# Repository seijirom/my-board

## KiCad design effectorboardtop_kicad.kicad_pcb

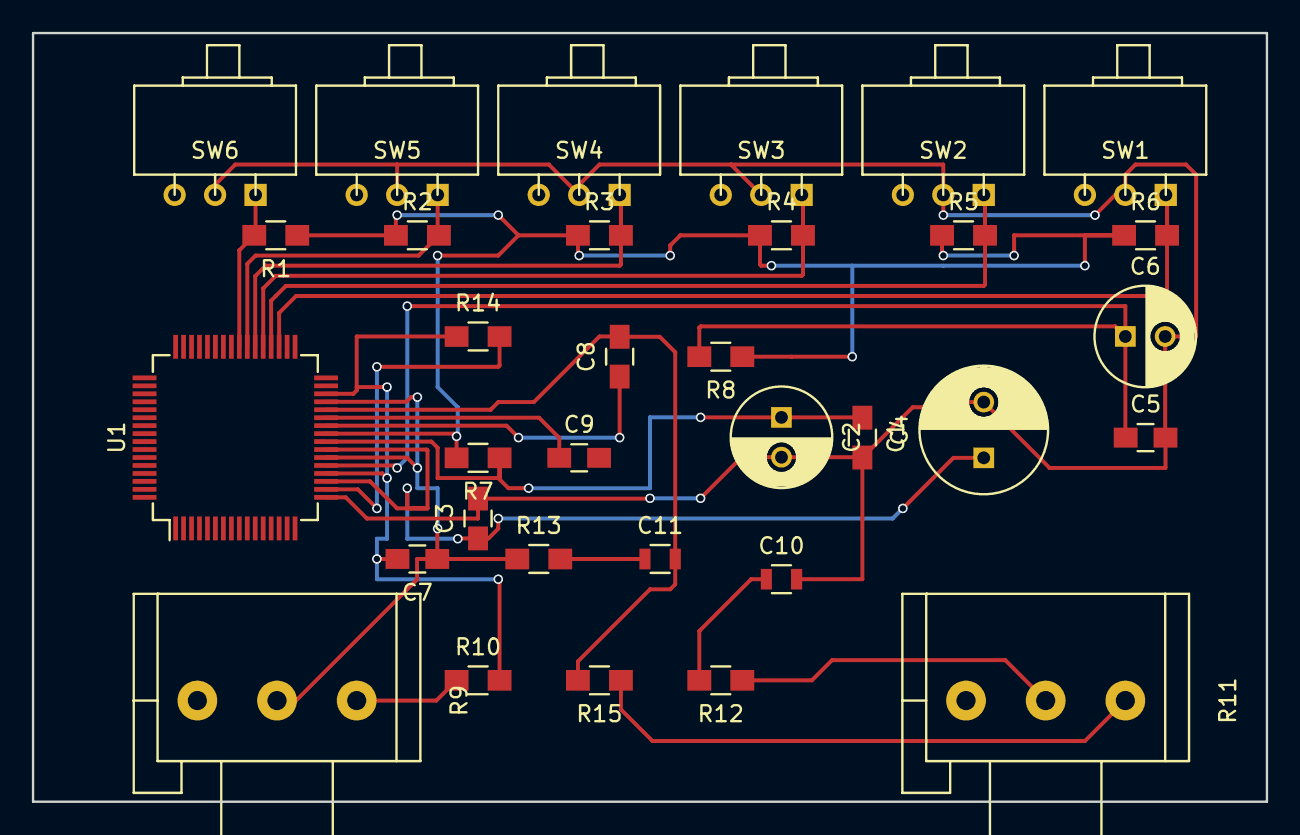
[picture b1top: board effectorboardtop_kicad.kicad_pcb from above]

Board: 2 copper layers, 77.5 x 48.3 mm, 33 parts (0 on the bottom side), 22 nets.

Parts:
C1, C3, C5: 0.1u; C_0805_HandSoldering
C2, C6: 100u; C_Radial_D6.3_L11.2_P2.5
C4: 470u; C_Radial_D8_L11.5_P3.5
C7: 47p; C_0805_HandSoldering
C8: 100p; C_0805_HandSoldering
C9: 0.047u; C_0805_HandSoldering
C10: 0.1u; R_0805
C11: 0.47u; R_0805
R1, R2, R3, R4, R5, R6, R12: 47k; R_0805_HandSoldering
R7, R8: 67k; R_0805_HandSoldering
R9: 500k; Potentiometer_Alps-RK16-single
R10, R13, R15: 10k; R_0805_HandSoldering
R11: 47k; Potentiometer_Alps-RK16-single
R14: 20k; R_0805_HandSoldering
SW1, SW2, SW3, SW4, SW5, SW6: SPST; SW_Micro_SPST_Angled
U1: QFP05-64; TQFP-64_10x10mm_Pitch0.5mm

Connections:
GND: C1.2, C2.2, C3.2, C4.2, C5.2, C6.2, C10.2, SW1.2, SW2.2, SW3.2, SW4.2, SW5.2, SW6.2, U1.17
unnamed: R1.1, R2.1, R3.1, R4.1, R5.1, R6.1, R7.2, R8.1, U1.25
unnamed: C1.1, C2.1, R7.1, U1.24
unnamed: C3.1, C4.1, U1.19, U1.23
unnamed: C5.1, C6.1, R8.2, U1.21
unnamed: C7.1, R9.2, R13.1, U1.22, U1.29
unnamed: C7.2, R10.2, R14.1, U1.20, U1.30
unnamed: C8.1, U1.26
unnamed: C9.1, U1.27
unnamed: C10.1, R12.2
unnamed: C11.1, R13.2
unnamed: C8.2, C11.2, R15.2, U1.28
unnamed: R14.2, U1.18
unnamed: R1.2, SW6.1, U1.40
unnamed: R2.2, SW5.1, U1.39
unnamed: R3.2, SW4.1, U1.38
unnamed: R4.2, SW3.1, U1.37
unnamed: R5.2, SW2.1, U1.36
unnamed: R6.2, SW1.1, U1.35
unnamed: R9.1, R10.1
unnamed: R11.1, R15.1
unnamed: R11.2, R12.1

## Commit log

2016-05-13 Add C:\Users\seijirom\AppData\Roaming\ALB\kicad\my_board_HEAD
2016-05-14 pcb layout first trial
2016-05-14 kicad_pcb added
2016-05-15 placement and routing completed
2016-05-15 before beta fill
